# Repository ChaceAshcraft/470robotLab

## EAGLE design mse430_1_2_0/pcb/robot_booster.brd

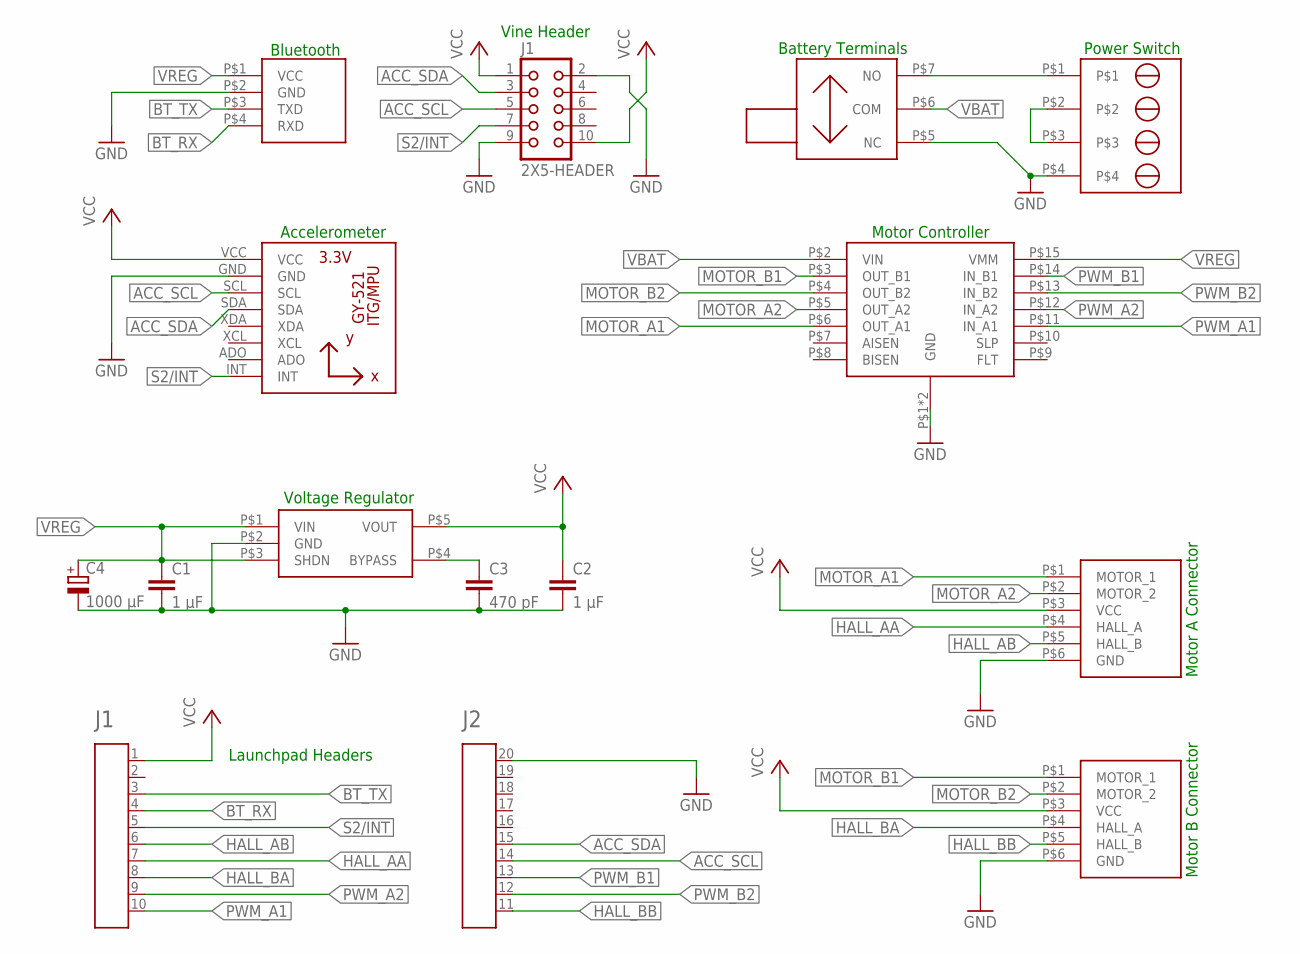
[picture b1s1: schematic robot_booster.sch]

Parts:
C1, C2: 1 µF; C0603
C3: 470 pF; C0603
C4: 1000 µF; E5-5
J1: 2X5-HEADER; 2X5_1.27MM_SMALL
U1: GY-521-HEADER
U$1: HEADER2X10-BOOSTERPACK; 2X10-BOOSTERPACK
U$2, U$3: POLOLU-MICROMETAL-ENCODER; 2MM-1X6-JST
U$4: POLOLU-DRV8833; HEADER-2X8-4W
U$5: TC1015; 5-PIN-SOT-23
U$6: HC06-RIGHT-ANGLE-HEADER; HEADER-4X1-RIGHT-ANGLE
U$7: 1X4-SCREW-TERMINAL-BLOCK-OSTTE040104; 1X04-SCREW-TERMINAL-BLOCK-OSTTE040104
U$8: SWITCH-EG1224; SWITCH-EG122-RIGHT-ANGLE

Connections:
ACC_SCL: J1.5, U1.SCL, U$1.14
ACC_SDA: J1.3, U1.SDA, U$1.15
BT_RX: U$1.4, U$6.P$4 (RXD)
BT_TX: U$1.3, U$6.P$3 (TXD)
GND: C1.2, C2.2, C3.2, C4.-, J1.2, J1.9, U1.GND, U$1.20, U$2.P$6 (GND), U$3.P$6 (GND), U$4.P$1 (GND), U$4.P$16 (GND), U$5.P$2 (GND), U$6.P$2 (GND), U$7.P$4, U$8.P$5 (NC)
HALL_AA: U$1.7, U$2.P$4 (HALL_A)
HALL_AB: U$1.6, U$2.P$5 (HALL_B)
HALL_BA: U$1.8, U$3.P$4 (HALL_A)
HALL_BB: U$1.11, U$3.P$5 (HALL_B)
MOTOR_A1: U$2.P$1 (MOTOR_1), U$4.P$6 (OUT_A1)
MOTOR_A2: U$2.P$2 (MOTOR_2), U$4.P$5 (OUT_A2)
MOTOR_B1: U$3.P$1 (MOTOR_1), U$4.P$3 (OUT_B1)
MOTOR_B2: U$3.P$2 (MOTOR_2), U$4.P$4 (OUT_B2)
unnamed: U$7.P$2, U$7.P$3
unnamed: U$7.P$1, U$8.P$7 (NO)
unnamed: C3.1, U$5.P$4 (BYPASS)
PWM_A1: U$1.10, U$4.P$11 (IN_A1)
PWM_A2: U$1.9, U$4.P$12 (IN_A2)
PWM_B1: U$1.13, U$4.P$14 (IN_B1)
PWM_B2: U$1.12, U$4.P$13 (IN_B2)
S2/INT: J1.7, U1.INT, U$1.5
VBAT: U$4.P$2 (VIN), U$8.P$6 (COM)
VCC: C2.1, J1.1, J1.10, U1.VCC, U$1.1, U$2.P$3 (VCC), U$3.P$3 (VCC), U$5.P$5 (VOUT)
VREG: C1.1, C4.+, U$4.P$15 (VMM), U$5.P$1 (VIN), U$5.P$3 (SHDN), U$6.P$1 (VCC)

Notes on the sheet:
Accelerometer
Motor Controller
Motor A Connector
Motor B Connector
Voltage Regulator
Power Switch
Battery Terminals
Launchpad Headers
Bluetooth
Vine Header

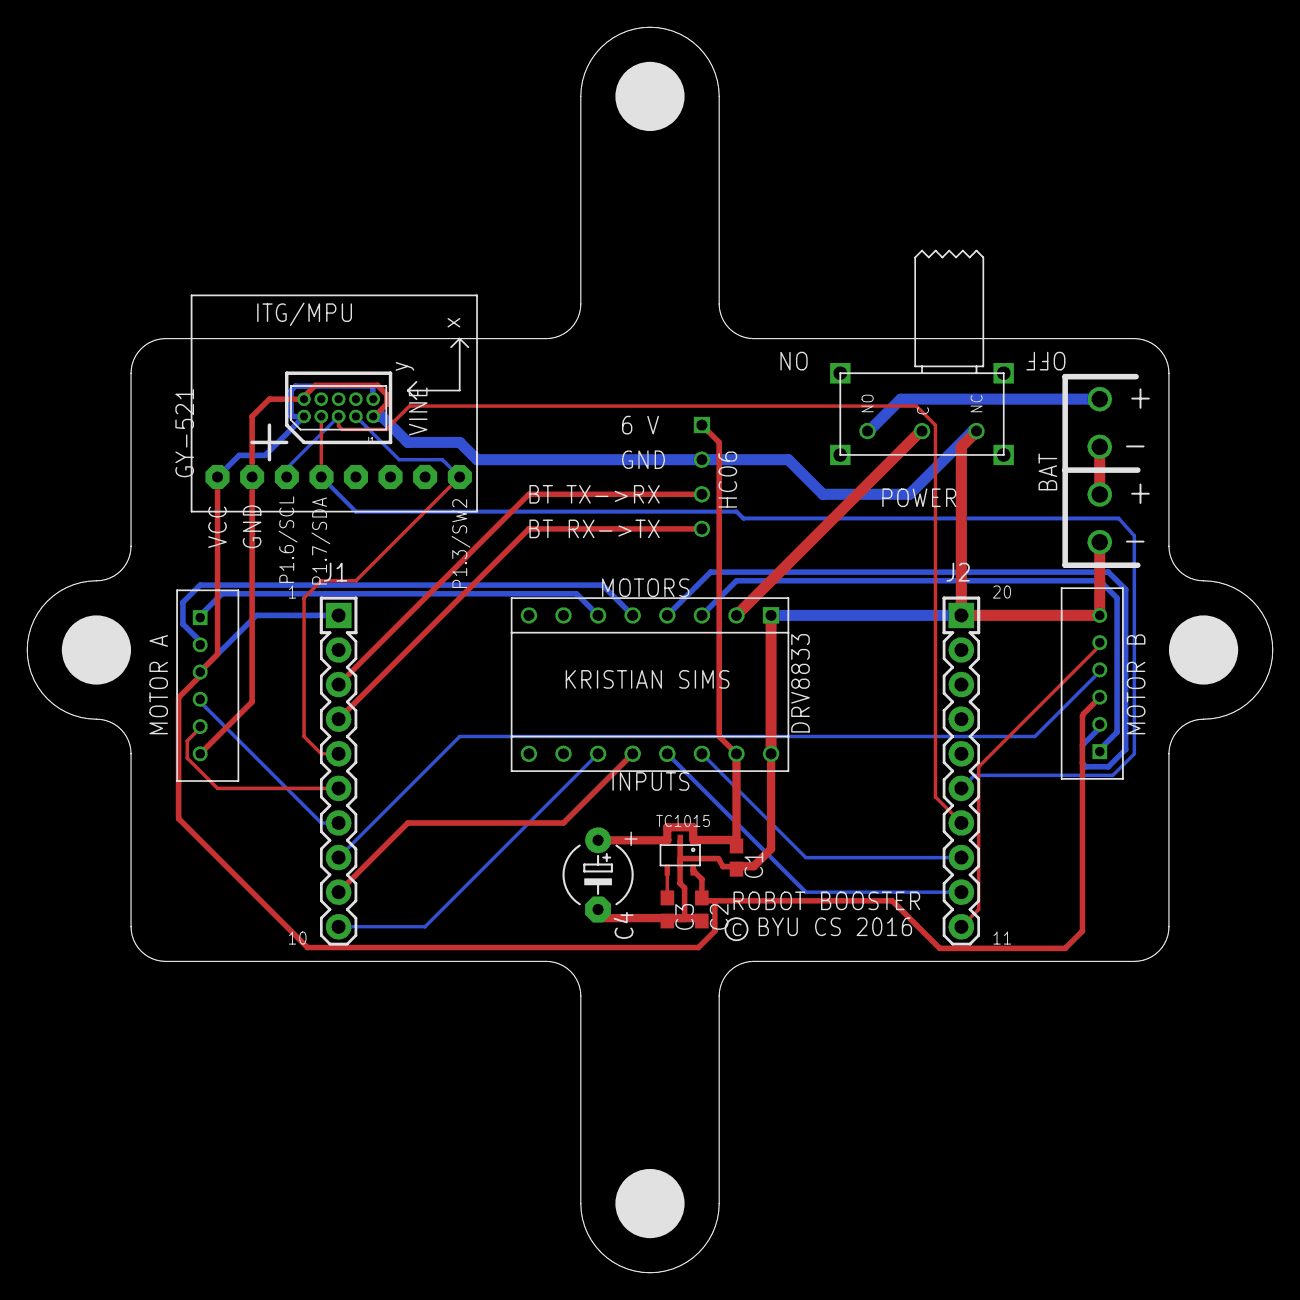
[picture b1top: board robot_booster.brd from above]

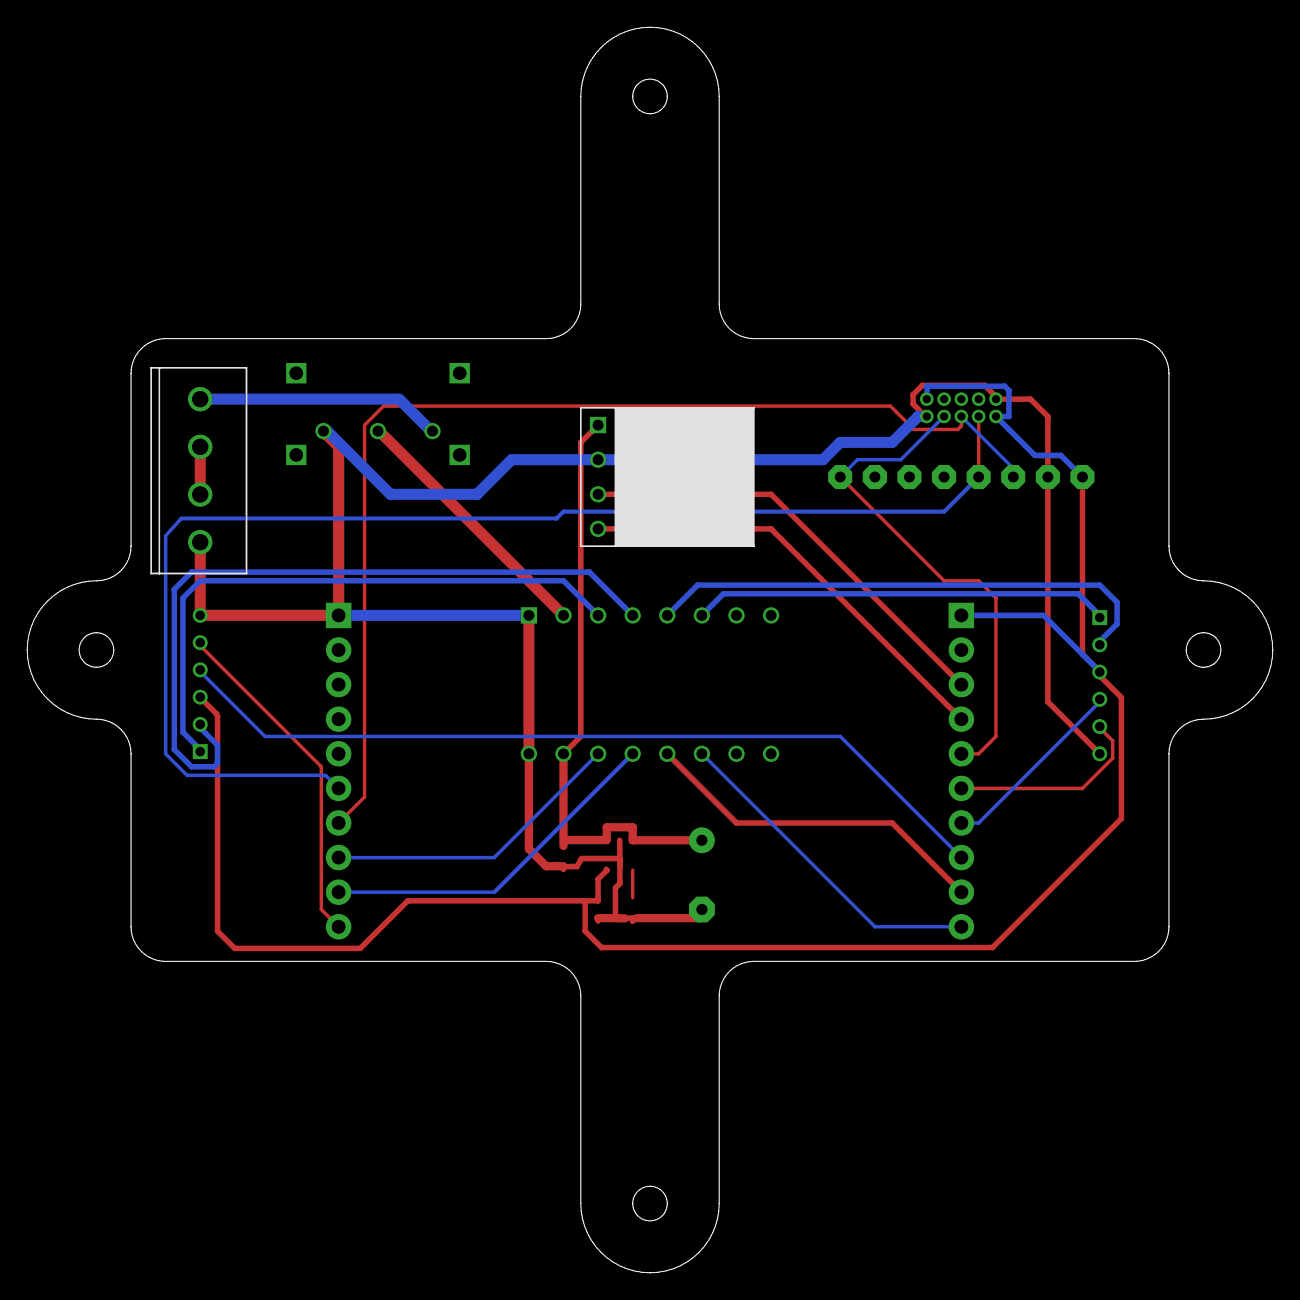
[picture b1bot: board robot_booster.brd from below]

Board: 2 copper layers, 91.4 x 91.4 mm, 14 parts (2 on the bottom side), 24 nets.

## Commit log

2017-09-27 added starter code
2017-09-28 got new updated files
2017-10-03 added start of potential fields lab file, and a potential fields class, if we want to use it.
2017-10-04 worked on potential fields lab, and created a special version for brian, because we couldn't agree on PIDs
2017-10-04 added some stuff to lab file
2017-10-05 JUST DO IT, BEFORE THIS DIES
2017-10-05 It might work now
2017-10-05 I feel commited now
2017-10-05 almost works!
2017-10-09 worked on it again, need to fix tangent fields
2017-10-10 worked more on the robot... still not quite happy
2017-10-11 added original implementation of potential fields to the file
2017-10-11 Added new old version of potential fields stuff
2017-10-11 Committing egregious errors to the project
2017-10-11 Some success!!!!
2017-10-11 added a file to test the select module for keyboard input
2017-10-12 tried part 2
2017-10-13 So frustrated...
2017-10-14 Finally... success!
2017-10-16 Reorganizing our code files (keeping it clean)
2017-10-17 Added the bases of the node and graph objects in the A* search
2017-10-17 Added a little more to A*
2017-10-17 implemented A*, hopefully correctly
2017-10-18 I am so committed to this relationship...code...stuff
2017-10-20 A* maybe ready to test
2017-10-20 tried out A*
2017-10-20 oh man... we did it wrong
2017-10-21 Got A* working... allegedly
2017-10-23 RRT Graph is about ready, just needs to be integrated in search_and_destroy.py. Get to it, Chace!
2017-10-23 RRT search is ready?
2017-10-23 getting closer!
2017-10-23 RRT search is ready! Path is now of locations!
2017-10-24 closer...
2017-10-24 made the robot move ever so slowly, but it worked for RRT
